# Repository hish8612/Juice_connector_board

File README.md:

# [Radioberry_Juice_connector_board](https://github.com/hish8612/Juice_connector_board)

 beta0.1 Release

This project provides information on how to build an [radioberry-juice](https://github.com/pa3gsb/Radioberry-2.x/tree/master/hardware/juice) using the FT2232HL Development Learning Board, available at low cost on Aliexpress and eBay. (abt. $13 to $18)<br>
Connector boards make it easy to connect the Radioberry-2 to the FT2232HL Learning Board.<br>

#### Juice View and Connection

<br>
<br>

#### Connetor board View
<br>
<br>

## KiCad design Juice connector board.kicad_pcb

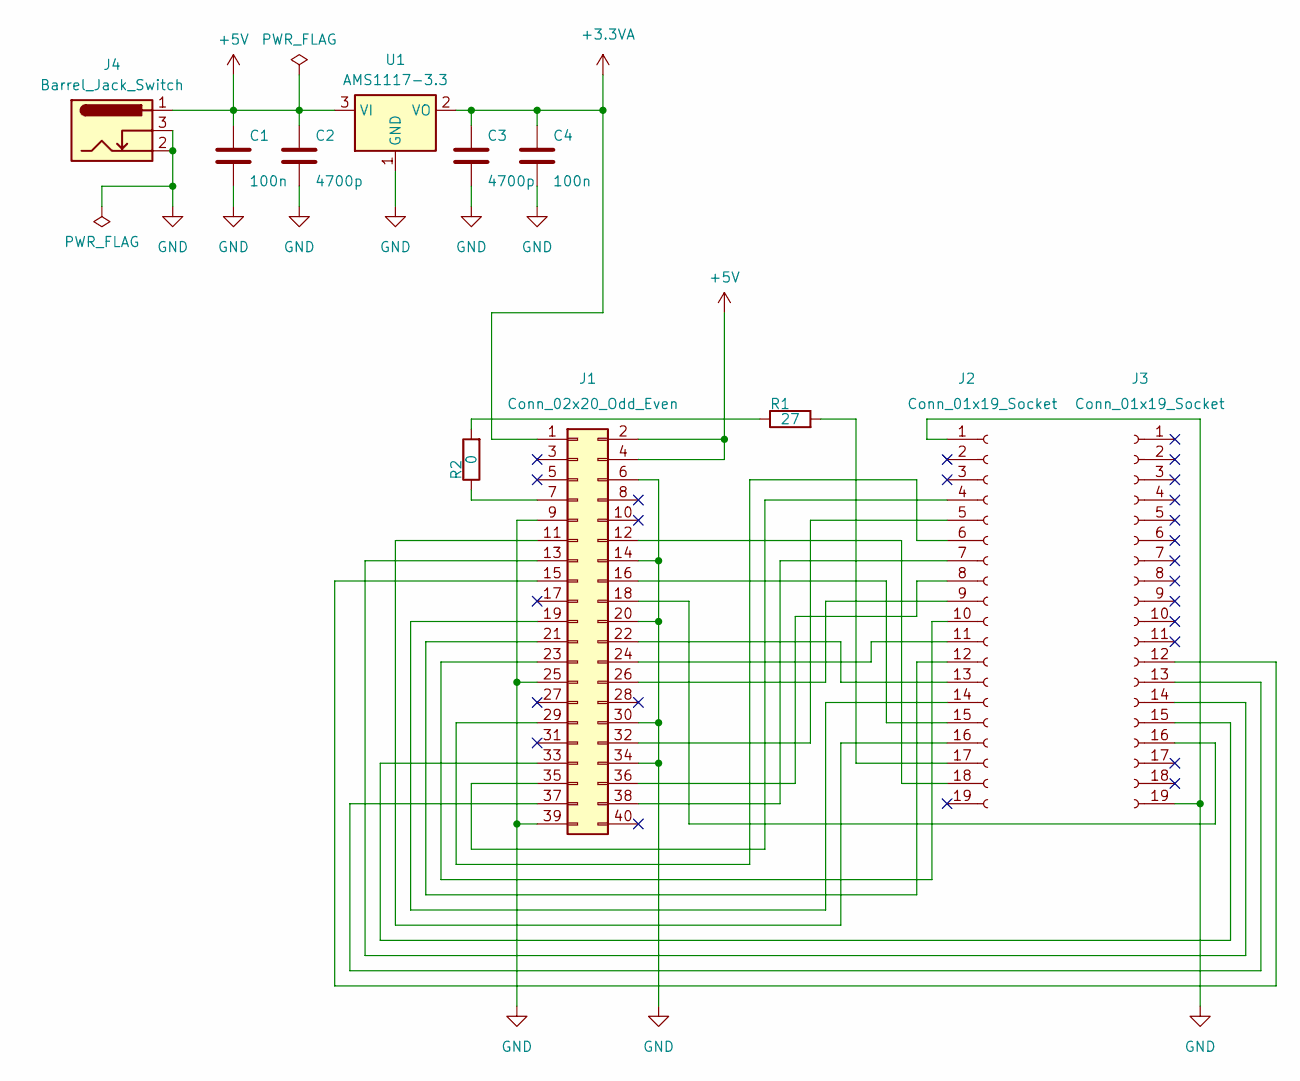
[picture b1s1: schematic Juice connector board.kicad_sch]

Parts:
C1, C4: 100n; C_0805_2012Metric
C2, C3: 4700p; C_0805_2012Metric
J1: Conn_02x20_Odd_Even; PinHeader_2x20_P2.54mm_Vertical
J2, J3: Conn_01x19_Socket; PinSocket_1x19_P2.54mm_Vertical
J4: Barrel_Jack_Switch; BarrelJack_Horizontal
R1: 27; R_0603_1608Metric
R2: 0; R_0603_1608Metric
U1: AMS1117-3.3; SOT-223-3_TabPin2

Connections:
+3.3VA: C3.1, C4.1, J1.1, U1.2 (VO)
+5V: C1.1, C2.1, J1.2, J1.4, J4.1, U1.3 (VI)
GND: C1.2, C2.2, C3.2, C4.2, J1.6, J1.9, J1.14, J1.20, J1.25, J1.30, J1.34, J1.39, J2.1, J3.19, J4.2, J4.3, U1.1 (GND)
unnamed: J1.7, R2.1
unnamed: J1.11, J2.16
unnamed: J1.12, J2.18
unnamed: J1.13, J3.14
unnamed: J1.15, J3.12
unnamed: J1.16, J2.15
unnamed: J1.18, J3.16
unnamed: J1.19, J2.14
unnamed: J1.21, J2.12
unnamed: J1.22, J2.13
unnamed: J1.23, J2.10
unnamed: J1.24, J2.11
unnamed: J1.26, J2.9
unnamed: J1.29, J2.6
unnamed: J1.32, J2.5
unnamed: J1.33, J3.15
unnamed: J1.35, J2.4
unnamed: J1.36, J2.8
unnamed: J1.37, J3.13
unnamed: J1.38, J2.7
unnamed: J2.17, R1.2
unnamed: R1.1, R2.2

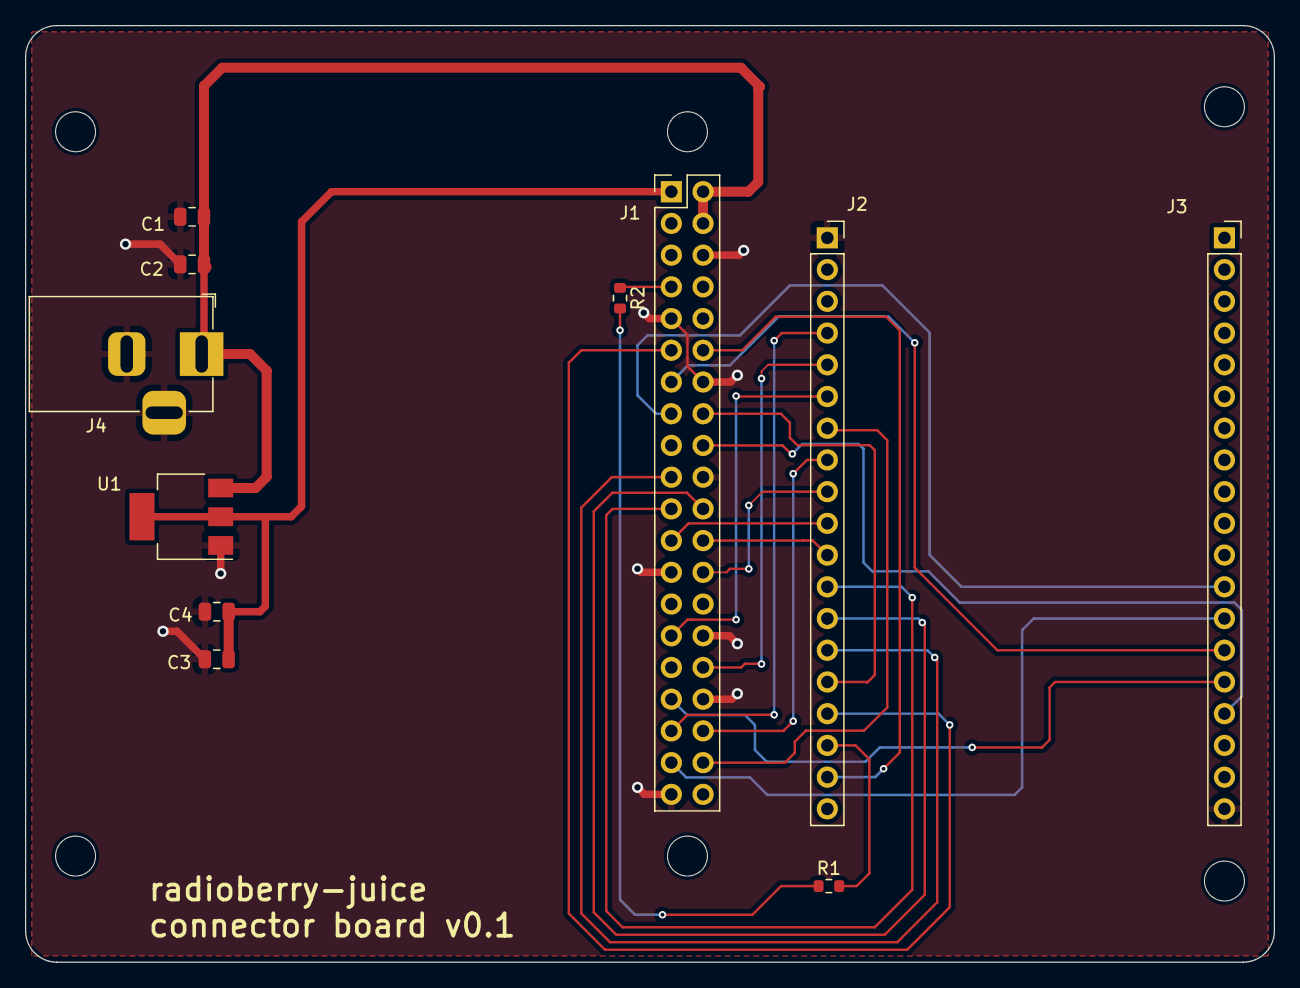
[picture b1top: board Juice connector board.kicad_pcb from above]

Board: 2 copper layers, 100.0 x 75.0 mm, 17 parts (0 on the bottom side), 25 nets.

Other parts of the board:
MH1, MH2, MH3, MH4, MH5, MH6: MountingHole_3.2mm_M3

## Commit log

2024-10-31 1st release beta0.1
2024-10-31 1st release, beta0.1
2024-12-13 Add the exe-file of the old version of the firmware.
